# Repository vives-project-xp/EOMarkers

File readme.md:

# **EO-Markers**

> Develop small standalone boxes that light up when someone approaches them.
> The boxes can be fitted with a plexi with Electronics-ICT and a
> direction indication via an arrow.

# Layout Github Repo

```bash
.
├── 3d tekening
│   ├── 3D_Bottom.png
│   ├── 3D_Main.png
│   └── README.md
├── Affiche
│   └── EO Markers Affiche.png
├── AndroidStudio
│   ├── EO-Markers
│   │   └── app
│   └── README.md
├── Arduino
│   ├── EO-Markers
│   │   ├── EO-Markers.cpp
│   │   └── EXAMPLE-config.h
│   └── README.md
├── img
│   ├── qr.png
│   └── project_canvas.png
│   └── potentiometers.jpg
│   └── schakelaar.jpg
├── PCB
│   ├── PCB
|   ├── PCB_ESP32-C3-DevKitM-1
│   ├── PCB_ESP32-C3-DevKitC-02
│   └── README.md
└── readme.md
```

# Table of contents

- [Planning](#planning)
- [Canvas](#canvas)
- [Affiche](#affiche)
- [How to use](#how-to-use)
- [3D Tekening](#3d-drawing)
- [Android Studio](#android-studio)
- [Arduino](#arduino)
- [PCB](#pcb)

# Planning

- sprint 1 - Uitwerken concept & BOM lijst doorgeven voor bestellingen
- sprint 2 - Van prototype naar product
- sprint 3 - Product afwerken en test klaar maken
- sprint 4 - Debuggen, documenteren

# Canvas

# Affiche

# How to use

1. It is important that the batteries are fully charged, as they are rechargeable. A USB-C port is provided as an alternative power supply.
2. Turn the switch on.

3. Wait about 10 seconds. The LED strips will then light up whenever the sensor, attached to the front of the marker, detects movement.
4. You can change the distance at which the sensor detects movement and the duration of lighting by turning the potentiometers as shown in the image.

5. Each time the light goes out, there is a period of 2.5 seconds before the sensor can detect movement again.
6. After using the EO marker, switch it off and charge the batteries.

# 3D drawing 

more info: [3D Tekening](./3d%20tekening/readme.md)

This is the base of the cube. The sensor is placed in the small round hole, the LED strips stick to the inside of the posts and the cables are inserted through the middle part. A reflective film has been applied to this area, which helps to spread the light around. A diffuser (plexiglass) is slid into the furthest slot and a plywood wall, with or without directions, is placed in the nearest slot.

This is the bottom of the cube. This is where the PCB, battery holder and cables end up. A hole is provided for a USB cable as secondary power. These 2 prints are screwed together with an M3 screw or bolt.

# Android Studio

more info: [Android Studio](./AndroidStudio/README.md)

# Arduino

more info: [Arduino](./Arduino/README.md)

# PCB

more info: [PCB](./PCB/README.md)

## PCB print

The PCB consists of a pair of connectors for the ESP, LED strip, sensor and USB-C port. These are female headers, so they fit in perfectly. The connectors are internally connected on the PCB. 

## PCB schematic

The circuit consists of 1 ESP, powered by a USB cable or a 5V battery pack connected in parallel on the j1 connector with a diode from battery pack to connector (4 rechargeable AA batteries). 3 female headers for the LED strips, 3 female headers for the sensor, 8 female headers for the USB-C port and a diode to stop current to the batteries.

Measurements:
U LED-strips (off): 4,1V;
U LED-strips (on): 3,1V

U Batteries (leds off): 4.9V;
U Batteries (leds on): 4.3V

U Diode (leds off): 0.72V;
U Diode (leds on): 0.86V

U Sensor (leds off): 2.98V;
U Sensor (leds on): 2.55V

U ESP (leds off): 4.1V;
U ESP (leds on): 3.45V

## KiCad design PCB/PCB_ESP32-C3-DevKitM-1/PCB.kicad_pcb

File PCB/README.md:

# PCB For EO-Marker

## Important Note

Use PCB_ESP32-C3-DevKitM-1 or PCB_ESP32-C3-DevKitC-02
but the pinout is the ***not*** same for both!

Physical layout is the same but the pinout is different.

Make sure to use the right code for the right esp32-c3-devkit.

Pinout:

|component|ESP32-C3-DevKitM-1|ESP32-C3-DevKitC-02|
|---|---|---|
|LED|GPIO 18|GPIO 19|
|Sensor|GPIO 10|GPIO 8|

## Table of Contents

- [layout](#layout)
- [PCB](#pcb-deprecated)
- [PCB_ESP32-C3-DevKitM-1](#pcb_esp32-c3-devkitc-02)
- [PCB_ESP32-C3-DevKitC-02](#pcb_esp32-c3-devkitc-02)

## layout

```bash
.
├── README.md
├── pcb
├── PCB_ESP32-C3-DevKitM-1
├── PCB_ESP32-C3-DevKitC-02

```

## PCB DEPRECATED

First version of PCB for EOMaker
is only for ESP32-C3-DevKitM-1.

Schematic and PCB:

### BOM

| Part | Value | Package | Description |
| --- | --- | --- | --- |
| J1 | Conn_01x08_Socket | Connector_PinSocket_2.54mm:PinSocket_1x08_P2.54mm_Vertical | Generic connector, single row, 01x08, script generated |
| LED1 | Conn_01x03_Socket | Connector_PinSocket_2.54mm:PinSocket_1x03_P2.54mm_Vertical | Generic connector, single row, 01x03, script generated |
| Sensor1 | Conn_01x03_Socket | Connector_PinSocket_2.54mm:PinSocket_1x03_P2.54mm_Vertical | Generic connector, single row, 01x03, script generated |
| U1 | ESP32-C3-DEVKITM-1 | ESP32-C3-DEVKITM-1:XCVR_ESP32-C3-DEVKITM-1 |  |

## PCB_ESP32-C3-DevKitM-1

### bom PCB_ESP32-C3-DevKitM-1

| Part | Value | Package | Description |
| --- | --- | --- | --- |
| J1 | Conn_01x08_Socket | Connector_PinSocket_2.54mm:PinSocket_1x08_P2.54mm_Vertical | Generic connector, single row, 01x08, script generated |
| LED1 | Conn_01x03_Socket | Connector_PinSocket_2.54mm:PinSocket_1x03_P2.54mm_Vertical | Generic connector, single row, 01x03, script generated |
| Q1, Q2 | NPN | Package_TO_SOT_SMD:SOT-23 | Bipolar transistor symbol for simulation only, substrate tied to the emitter |
| R1, R3 | 1KΩ | Resistor_SMD:R_0805_2012Metric | Resistor |
| R2, R4 | 10KΩ | Resistor_SMD:R_0805_2012Metric | Resistor |
| Sensor1 | Conn_01x03_Socket | Connector_PinSocket_2.54mm:PinSocket_1x03_P2.54mm_Vertical | Generic connector, single row, 01x03, script generated |
| U1 | ESP32-C3-DEVKITM-1 | ESP32-C3-DEVKITM-1:XCVR_ESP32-C3-DEVKITM-1 |  |

## PCB_ESP32-C3-DevKitC-02

### bom PCB_ESP32-C3-DevKitM-02

| Part | Value | Package | Description |
| --- | --- | --- | --- |
| J1 | Conn_01x08_Socket | Connector_PinSocket_2.54mm:PinSocket_1x08_P2.54mm_Vertical | Generic connector, single row, 01x08, script generated |
| LED1 | Conn_01x03_Socket | Connector_PinSocket_2.54mm:PinSocket_1x03_P2.54mm_Vertical | Generic connector, single row, 01x03, script generated |
| Q1, Q2 | NPN | Package_TO_SOT_SMD:SOT-23 | Bipolar transistor symbol for simulation only, substrate tied to the emitter |
| R1, R3 | 1KΩ | Resistor_SMD:R_0805_2012Metric | Resistor |
| R2, R4 | 10KΩ | Resistor_SMD:R_0805_2012Metric | Resistor |
| Sensor1 | Conn_01x03_Socket | Connector_PinSocket_2.54mm:PinSocket_1x03_P2.54mm_Vertical | Generic connector, single row, 01x03, script generated |
| U1 | ESP32-C3-DEVKITC-02 | ESP32-C3-DEVKITC-02:XCVR_ESP32-C3-DEVKITC-02 |  |

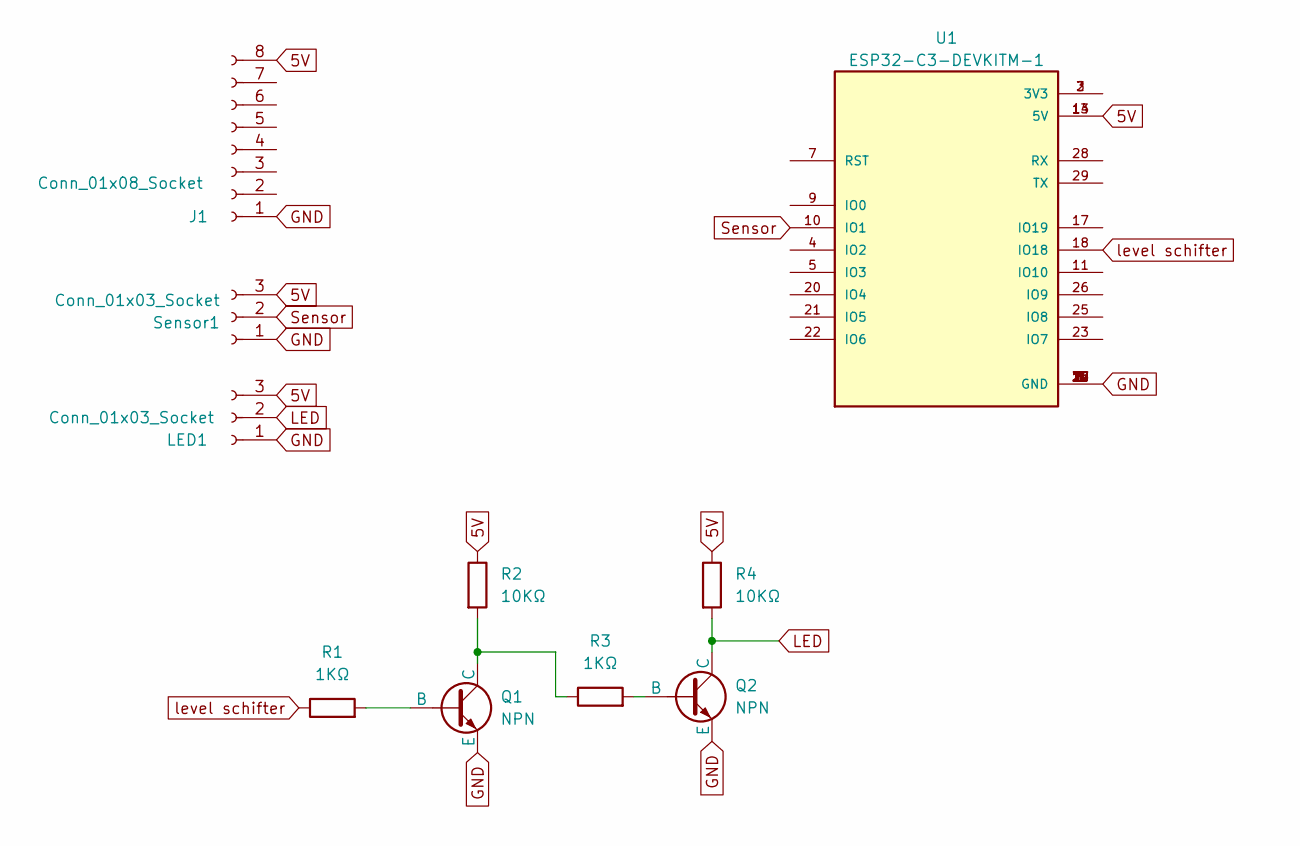
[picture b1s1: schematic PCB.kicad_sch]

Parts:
J1: Conn_01x08_Socket; PinSocket_1x08_P2.54mm_Vertical
LED1: Conn_01x03_Socket; PinSocket_1x03_P2.54mm_Vertical
Q1, Q2: NPN; SOT-23
R1, R3: 1KΩ; R_0805_2012Metric
R2, R4: 10KΩ; R_0805_2012Metric
Sensor1: Conn_01x03_Socket; PinSocket_1x03_P2.54mm_Vertical
U1: ESP32-C3-DEVKITM-1; XCVR_ESP32-C3-DEVKITM-1

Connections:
5V: J1.8, LED1.3, R2.1, R4.1, Sensor1.3, U1.13 (5V), U1.14 (5V)
GND: J1.1, LED1.1, Q1.3 (E), Q2.3 (E), Sensor1.1, U1.1 (GND), U1.6 (GND), U1.8 (GND), U1.12 (GND), U1.15 (GND), U1.16 (GND), U1.19 (GND), U1.24 (GND), U1.27 (GND), U1.30 (GND)
LED: LED1.2, Q2.1 (C), R4.2
unnamed: Q1.2 (B), R1.2
unnamed: Q1.1 (C), R2.2, R3.1
unnamed: Q2.2 (B), R3.2
unnamed: U1.2 (3V3), U1.3 (3V3)
Sensor: Sensor1.2, U1.10 (IO1)
level schifter: R1.1, U1.18 (IO18)

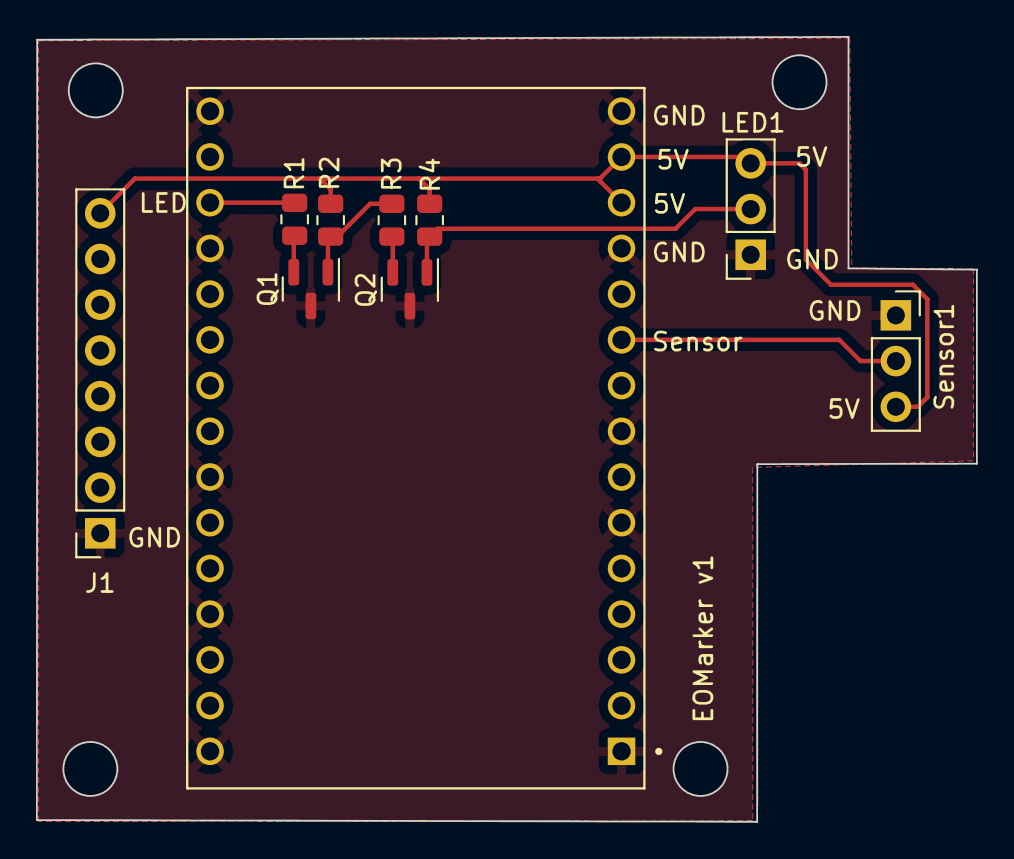
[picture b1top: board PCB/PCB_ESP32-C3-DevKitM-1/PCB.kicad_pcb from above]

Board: 2 copper layers, 52.2 x 43.6 mm, 10 parts (0 on the bottom side), 9 nets.

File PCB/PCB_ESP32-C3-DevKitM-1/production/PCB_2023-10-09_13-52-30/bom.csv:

Designator,Footprint,Quantity,Value,LCSC Part #
"LED, Sensor",PinSocket_1x03_P2.54mm_Vertical,2,Conn_01x03_Socket,
U1,XCVR_ESP32-C3-DEVKITM-1,1,ESP32-C3-DEVKITM-1,

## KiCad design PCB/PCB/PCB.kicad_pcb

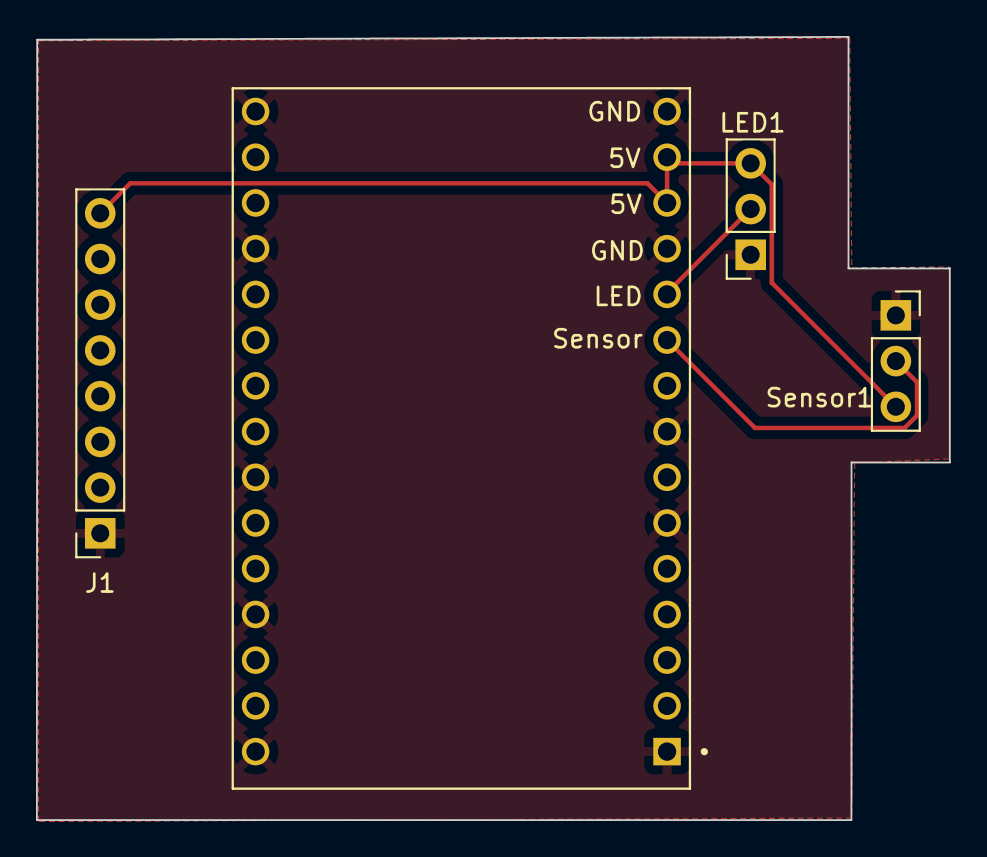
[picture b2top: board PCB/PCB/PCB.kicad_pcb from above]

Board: 2 copper layers, 50.7 x 43.5 mm, 4 parts (0 on the bottom side), 5 nets.

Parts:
J1: USB-C; PinSocket_1x08_P2.54mm_Vertical
LED1: Conn_01x03_Socket; PinSocket_1x03_P2.54mm_Vertical
Sensor1: Conn_01x03_Socket; PinSocket_1x03_P2.54mm_Vertical
U1: ESP32-C3-DEVKITM-1; XCVR_ESP32-C3-DEVKITM-1

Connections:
5V: J1.8, LED1.3, Sensor1.3, U1.13 (5V), U1.14 (5V)
GND: J1.1, LED1.1, Sensor1.1, U1.1 (GND), U1.6 (GND), U1.8 (GND), U1.12 (GND), U1.15 (GND), U1.16 (GND), U1.19 (GND), U1.24 (GND), U1.27 (GND), U1.30 (GND)
LED: LED1.2, U1.11 (IO10)
unnamed: U1.2 (3V3), U1.3 (3V3)
Sensor: Sensor1.2, U1.10 (IO1)

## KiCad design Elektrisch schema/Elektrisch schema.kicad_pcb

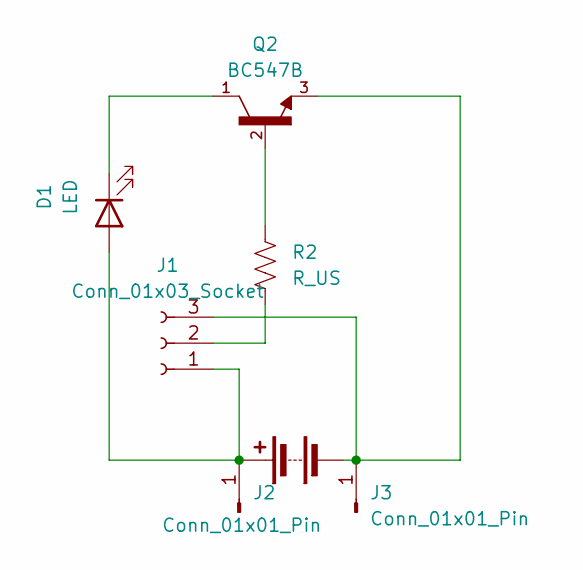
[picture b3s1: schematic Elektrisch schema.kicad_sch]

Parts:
BT1: Battery; BatteryHolder_Keystone_2462_2xAA
D1: LED; LED_D5.0mm
J1: Conn_01x03_Socket; PinHeader_1x03_P2.54mm_Vertical
J2, J3: Conn_01x01_Pin; PinHeader_1x01_P2.54mm_Vertical
Q2: BC547B; TO92250P510H770-3
R2: R_US; R_0805_2012Metric

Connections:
unnamed: BT1.1 (+), D1.2 (A), J1.1, J2.1
unnamed: BT1.2 (-), J1.3, J3.1, Q2.3
unnamed: D1.1 (K), Q2.1
unnamed: J1.2, R2.2
unnamed: Q2.2, R2.1

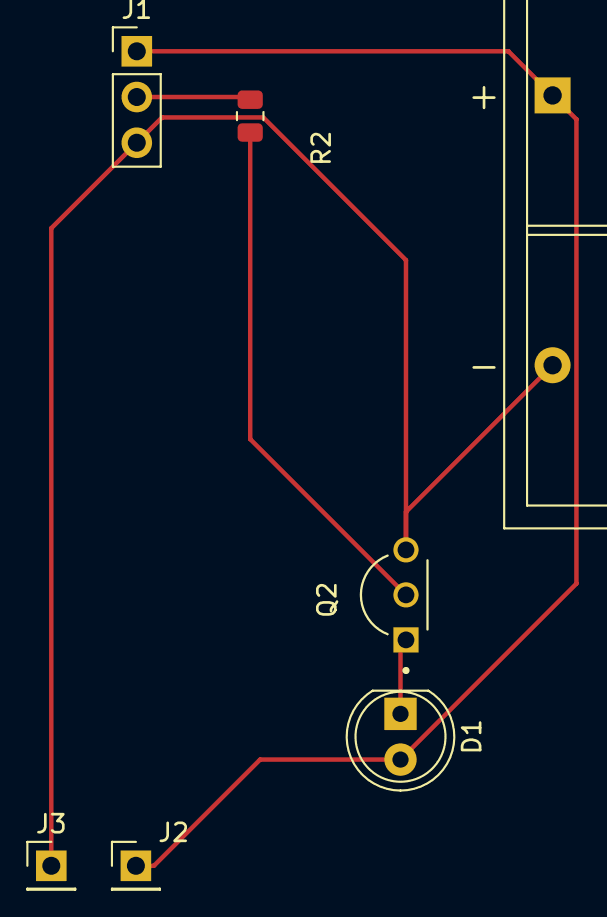
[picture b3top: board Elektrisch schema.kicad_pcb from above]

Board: 2 copper layers, 7 parts (0 on the bottom side), 5 nets.

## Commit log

2023-09-18 added readme
2023-09-19 adding canvas_project.pdf in img folder
2023-09-25 Added affiche
2023-09-25 Elektrisch schema first draft
2023-09-25 elektisch shema second draft
2023-10-02 concept affiche
2023-10-02 toevoeging 3d tekening
2023-10-02 updated 3d tekening
2023-10-02 updating github
2023-10-02 3d tekening aangepast + 2d tekening
2023-10-09 Added arduino program
2023-10-09 added android studio project
2023-10-09 PCB getekend
2023-10-09 created app to control leds
2023-10-16 added config file to arduino
2023-10-16 added mqtt alive
2023-10-16 Added config file to android studio
2023-10-16 deleted unused pcb files
2023-10-16 updated arduino
2023-10-16 Readme bijgevuld en schema gemaakt
2023-10-16 Added example config
2023-10-16 refacter ino code
2023-10-16 affiche aangepast
2023-10-19 cleaned arduino code
2023-10-23 Fixed rgb code
2023-10-23 added background task for wifi
2023-10-23 cleaned code
2023-10-30 3d drawing updated
2023-11-05 adding arduino flowchart
2023-11-05 editing arduino flowchart
2023-11-06 Added broker url to strings file
2023-11-06 added support for USB-C port
2023-11-06 shortened the pillar for space for the batterypack
2023-11-06 added settings tab to app
2023-11-06 3d drawing adjusted for 4th slide
2023-11-06 added device dropdown to app
2023-11-06 made more space for sensor
2023-11-06 update van affiche
2023-11-06 plaats voor schakelaar
2023-11-13 added device ab to app
2023-11-20 Fully working app
2023-12-01 cleanup android code
2023-12-04 Added color All to android app
2023-12-10 re naming arduino example config file
2023-12-10 adding more pcb versions and a readme with explenation
2023-12-11 minor readme change
2023-12-11 updateting canvas
2023-12-11 update affiche
2023-12-11 Delete Elektrisch schema directory
    redundant already in pcb folder
2023-12-11 new update affiche
2023-12-11 updating main readme
2023-12-11 adding readmes in arduino and androidstudio folders
2023-12-11 readme 3d tekening
2023-12-11 name change
2023-12-11 Delete Elektrisch schema/Elektrisch schema-backups directory
    redundant folder
2023-12-11 Fixed arduino + android code
2023-12-18 android studio
2023-12-18 arduino
2023-12-18 readme and images
